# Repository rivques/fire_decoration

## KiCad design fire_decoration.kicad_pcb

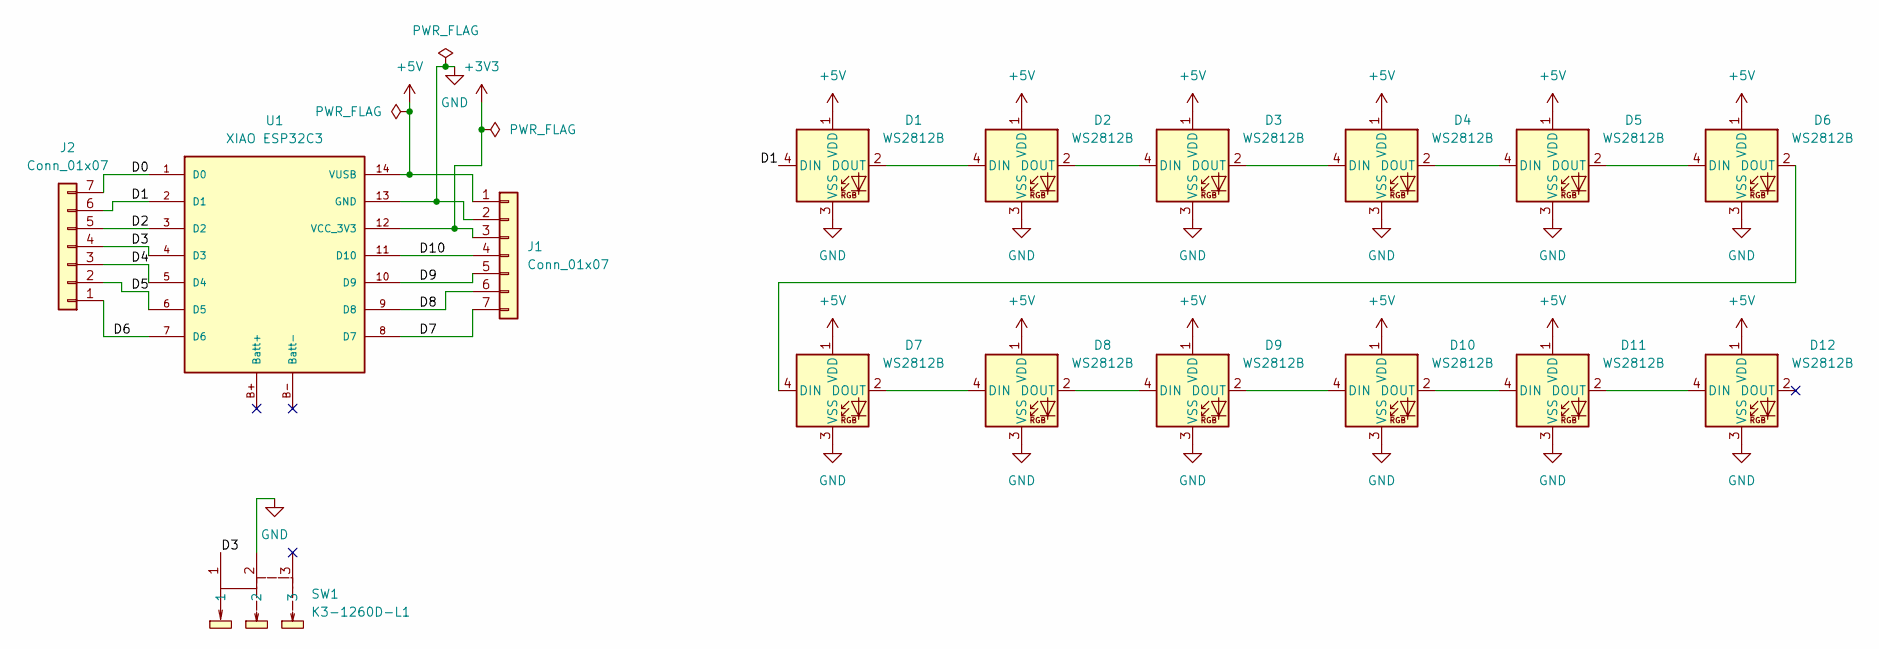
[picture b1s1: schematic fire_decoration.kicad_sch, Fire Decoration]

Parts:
D1, D2, D3, D4, D5, D6, D7, D8, D9, D10, D11, D12: WS2812B; LED_WS2812B_PLCC4_5.0x5.0mm_P3.2mm
J1, J2: Conn_01x07; PinSocket_1x07_P2.54mm_Vertical
SW1: K3-1260D-L1; SW-TH_K3-1260D-L1; LCSC Part C92657
U1: XIAO ESP32C3; xiao_esp32c3

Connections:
+3V3: J1.3, U1.12 (VCC_3V3)
+5V: D1.1 (VDD), D2.1 (VDD), D3.1 (VDD), D4.1 (VDD), D5.1 (VDD), D6.1 (VDD), D7.1 (VDD), D8.1 (VDD), D9.1 (VDD), D10.1 (VDD), D11.1 (VDD), D12.1 (VDD), J1.1, U1.14 (VUSB)
/D0: J2.7, U1.1 (D0)
/D1: D1.4 (DIN), J2.6, U1.2 (D1)
/D2: J2.5, U1.3 (D2)
/D3: J2.4, SW1.1, U1.4 (D3)
/D4: J2.3, U1.5 (D4)
/D5: J2.2, U1.6 (D5)
/D6: J2.1, U1.7 (D6)
/D7: J1.7, U1.8 (D7)
/D8: J1.6, U1.9 (D8)
/D9: J1.5, U1.10 (D9)
/D10: J1.4, U1.11 (D10)
GND: D1.3 (VSS), D2.3 (VSS), D3.3 (VSS), D4.3 (VSS), D5.3 (VSS), D6.3 (VSS), D7.3 (VSS), D8.3 (VSS), D9.3 (VSS), D10.3 (VSS), D11.3 (VSS), D12.3 (VSS), J1.2, SW1.2, U1.13 (GND)
unnamed: D1.2 (DOUT), D2.4 (DIN)
unnamed: D2.2 (DOUT), D3.4 (DIN)
unnamed: D3.2 (DOUT), D4.4 (DIN)
unnamed: D4.2 (DOUT), D5.4 (DIN)
unnamed: D5.2 (DOUT), D6.4 (DIN)
unnamed: D6.2 (DOUT), D7.4 (DIN)
unnamed: D7.2 (DOUT), D8.4 (DIN)
unnamed: D8.2 (DOUT), D9.4 (DIN)
unnamed: D9.2 (DOUT), D10.4 (DIN)
unnamed: D10.2 (DOUT), D11.4 (DIN)
unnamed: D11.2 (DOUT), D12.4 (DIN)

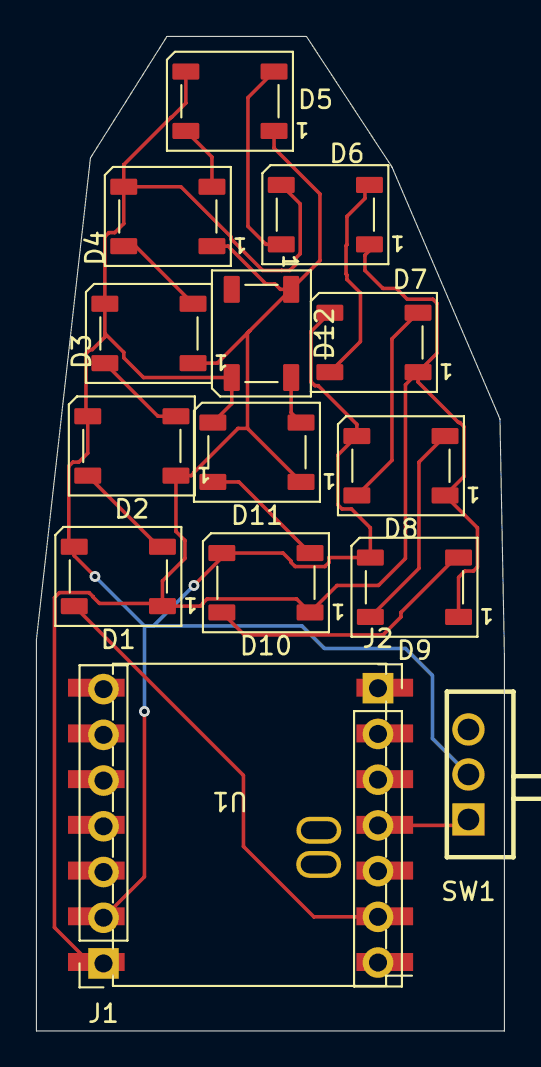
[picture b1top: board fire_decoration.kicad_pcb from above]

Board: 2 copper layers, 26.0 x 55.2 mm, 16 parts (0 on the bottom side), 25 nets.

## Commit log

2024-12-22 add kicad files
